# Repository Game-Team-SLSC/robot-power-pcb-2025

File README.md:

# Game Team's robot power pcb for Eurobot Junior 2025

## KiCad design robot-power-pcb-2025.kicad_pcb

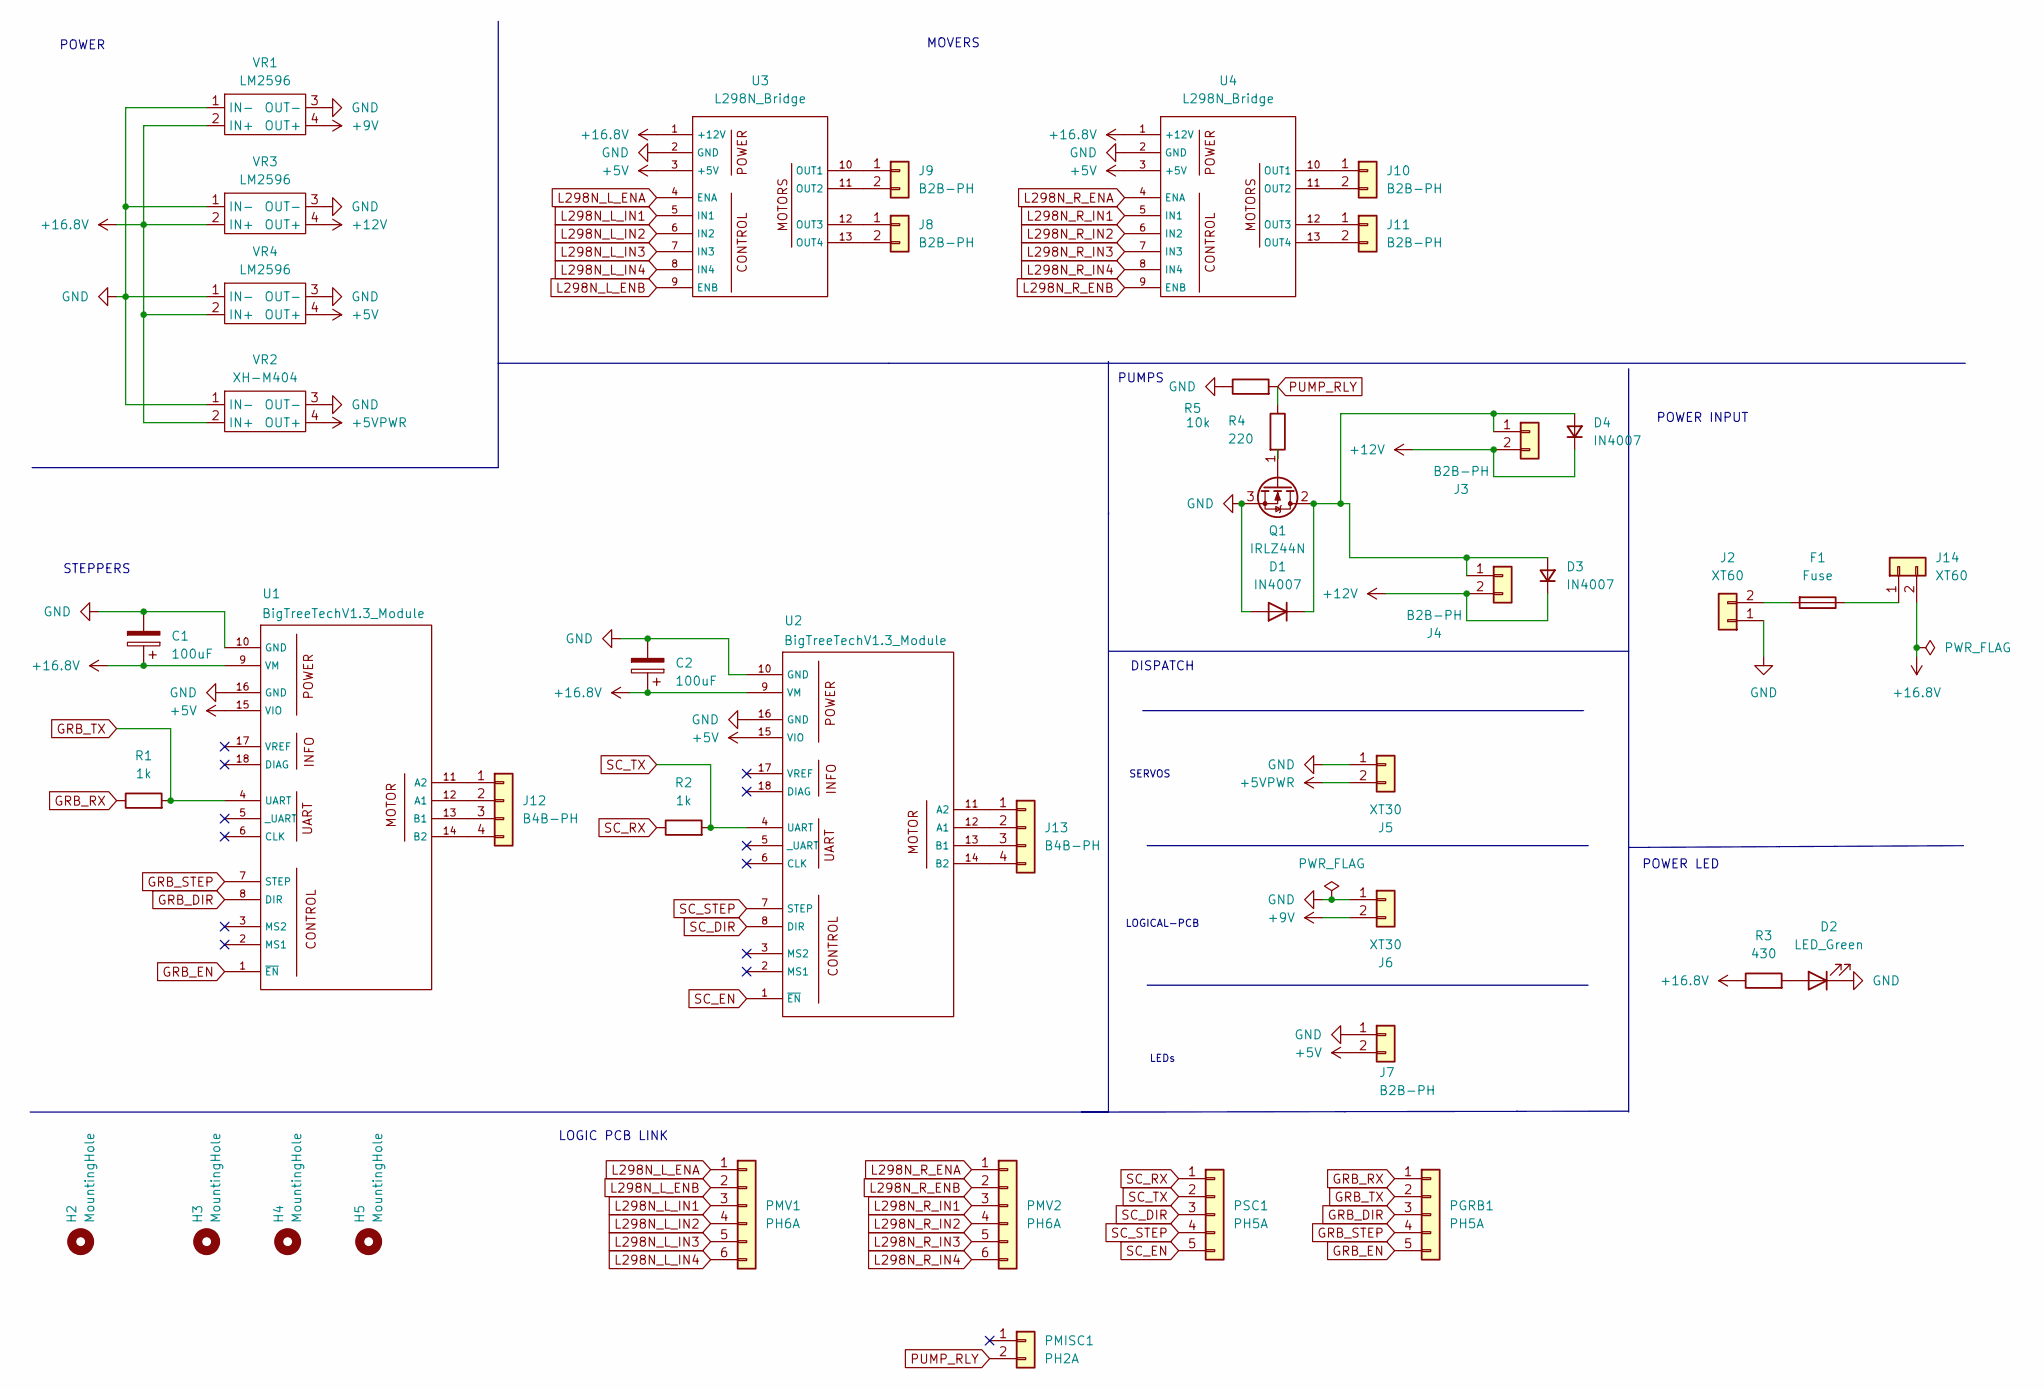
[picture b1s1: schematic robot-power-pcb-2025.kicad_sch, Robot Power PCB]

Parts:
C1, C2: 100uF; CP_Radial_D6.3mm_P2.50mm
D1, D3, D4: IN4007; D_DO-41_SOD81_P2.54mm_Vertical_AnodeUp
D2: LED_Green; LED_D5.0mm
F1: Fuse; Fuseholder_Cylinder-5x20mm_Schurter_0031_8201_Horizontal_Op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
H2, H3, H4, H5: MountingHole; MountingHole_2.7mm_M2.5
J2, J14: XT60; AMASS_XT60-M_1x02_P7.20mm_Vertical
J3, J4, J7, J8, J9, J10, J11: B2B-PH; JST_PH_B2B-PH-K_1x02_P2.00mm_Vertical
J5, J6: XT30; AMASS_XT30U-M_1x02_P5.0mm_Vertical
J12, J13: B4B-PH; JST_PH_B4B-PH-K_1x04_P2.00mm_Vertical
PGRB1: PH5A; JST_PH_B5B-PH-K_1x05_P2.00mm_Vertical
PMISC1: PH2A; JST_PH_B2B-PH-K_1x02_P2.00mm_Vertical
PMV1, PMV2: PH6A; JST_PH_B6B-PH-K_1x06_P2.00mm_Vertical
PSC1: PH5A; JST_PH_B5B-PH-K_1x05_P2.00mm_Vertical
Q1: IRLZ44N; TO-220-3_Horizontal_TabDown
R1, R2: 1k; R_Axial_DIN0207_L6.3mm_D2.5mm_P7.62mm_Horizontal
R3: 430; R_Axial_DIN0207_L6.3mm_D2.5mm_P7.62mm_Horizontal
R4: 220; R_Axial_DIN0207_L6.3mm_D2.5mm_P7.62mm_Horizontal
R5: 10k; R_Axial_DIN0207_L6.3mm_D2.5mm_P7.62mm_Horizontal
U1, U2: BigTreeTechV1.3_Module; TMC2209
U3, U4: L298N_Bridge
VR1, VR3, VR4: LM2596
VR2: XH-M404; XHM404_Module

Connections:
+5V: J7.2, U1.15 (VIO), U2.15 (VIO), U3.3 (+5V), U4.3 (+5V), VR4.4 (OUT+)
+5VPWR: J5.2, VR2.4 (OUT+)
+9V: J6.2, VR1.4 (OUT+)
+12V: D3.1 (K), D4.1 (K), J3.2, J4.2, VR3.4 (OUT+)
+16.8V: C1.1, C2.1, J14.2, R3.1, U1.9 (VM), U2.9 (VM), U3.1 (+12V), U4.1 (+12V), VR1.2 (IN+), VR2.2 (IN+), VR3.2 (IN+), VR4.2 (IN+)
GND: C1.2, C2.2, D1.2 (A), D2.1 (K), J2.1, J5.1, J6.1, J7.1, Q1.3 (S), R5.1, U1.10 (GND), U1.16 (GND), U2.10 (GND), U2.16 (GND), U3.2 (GND), U4.2 (GND), VR1.1 (IN-), VR1.3 (OUT-), VR2.1 (IN-), VR2.3 (OUT-), VR3.1 (IN-), VR3.3 (OUT-), VR4.1 (IN-), VR4.3 (OUT-)
GRB_DIR: PGRB1.3, U1.8 (DIR)
GRB_EN: PGRB1.5, U1.1 (~EN)
GRB_RX: PGRB1.1, R1.1
GRB_STEP: PGRB1.4, U1.7 (STEP)
GRB_TX: PGRB1.2, R1.2, U1.4 (UART)
L298N_L_ENA: PMV1.1, U3.4 (ENA)
L298N_L_ENB: PMV1.2, U3.9 (ENB)
L298N_L_IN1: PMV1.3, U3.5 (IN1)
L298N_L_IN2: PMV1.4, U3.6 (IN2)
L298N_L_IN3: PMV1.5, U3.7 (IN3)
L298N_L_IN4: PMV1.6, U3.8 (IN4)
L298N_R_ENA: PMV2.1, U4.4 (ENA)
L298N_R_ENB: PMV2.2, U4.9 (ENB)
L298N_R_IN1: PMV2.3, U4.5 (IN1)
L298N_R_IN2: PMV2.4, U4.6 (IN2)
L298N_R_IN3: PMV2.5, U4.7 (IN3)
L298N_R_IN4: PMV2.6, U4.8 (IN4)
unnamed: D1.1 (K), D3.2 (A), D4.2 (A), J3.1, J4.1, Q1.2 (D)
unnamed: D2.2 (A), R3.2
unnamed: F1.2, J2.2
unnamed: J8.1, U3.12 (OUT3)
unnamed: J8.2, U3.13 (OUT4)
unnamed: J9.1, U3.10 (OUT1)
unnamed: J9.2, U3.11 (OUT2)
unnamed: J10.1, U4.10 (OUT1)
unnamed: J10.2, U4.11 (OUT2)
unnamed: J11.1, U4.12 (OUT3)
unnamed: J11.2, U4.13 (OUT4)
unnamed: J12.1, U1.11 (A2)
unnamed: J12.2, U1.12 (A1)
unnamed: J12.3, U1.13 (B1)
unnamed: J12.4, U1.14 (B2)
unnamed: J13.1, U2.11 (A2)
unnamed: J13.2, U2.12 (A1)
unnamed: J13.3, U2.13 (B1)
unnamed: J13.4, U2.14 (B2)
unnamed: F1.1, J14.1
unnamed: Q1.1 (G), R4.2
PUMP_RLY: PMISC1.2, R4.1, R5.2
SC_DIR: PSC1.3, U2.8 (DIR)
SC_EN: PSC1.5, U2.1 (~EN)
SC_RX: PSC1.1, R2.1
SC_STEP: PSC1.4, U2.7 (STEP)
SC_TX: PSC1.2, R2.2, U2.4 (UART)

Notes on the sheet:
LOGIC PCB LINK
POWER
POWER LED
DISPATCH
POWER INPUT
SERVOS
STEPPERS
MOVERS
LOGICAL-PCB
LEDs
PUMPS

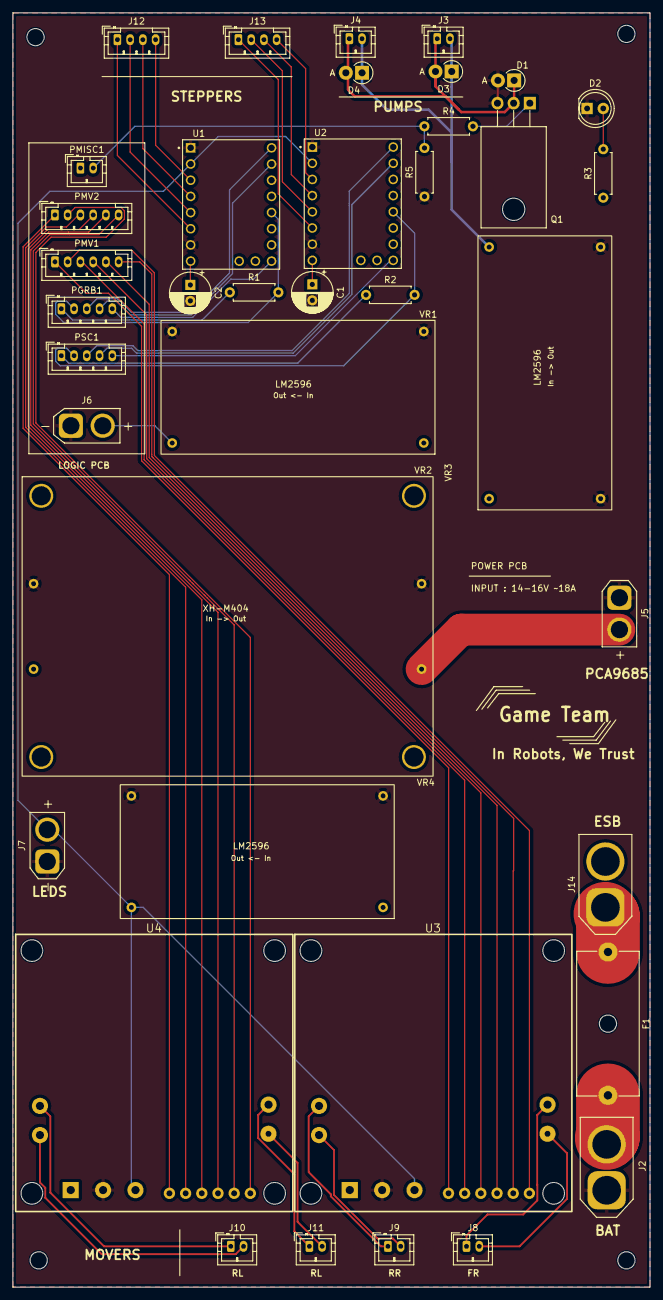
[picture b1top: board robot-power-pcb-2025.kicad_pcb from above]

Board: 2 copper layers, 100.0 x 200.0 mm, 43 parts (0 on the bottom side), 50 nets.

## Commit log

2025-02-04 fix schematics
2025-02-06 Run to fab
2025-02-07 fixes
2025-03-14 Add logo
